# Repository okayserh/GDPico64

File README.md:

# GDPico64
Raspberry pico based graphics card to emulate an 80s EF9365 based graphics card to be used in conjunction with a modular 8 bit Z80 based computer system.

# Background
In the mid/late 80s, german public television broadcasted a series of 26 episodes of a stepwise introduction to microcomputer technology. It started with the usual stuff like binary logic, memory and the purpose of a central processing unit. Parallel to the explanations the series worked on building a modular 8 bit microcomputer, which was based on an 8 bit bus system. While the basic system used the Z80 CPU, it was possible to extend the system to an 68008 CPU board and with some tricks even to an 68020 CPU.
A full set of information and the required software is available on the following website (most of it is in german language):
www.ndr-nkc.de
In its modular setup it is conceptually very similar to the RC2014* project.

# Project
One cornerstone of the modular computer system was the graphics card named GDP64, where the 64 stands for 64kB of dedicated graphics memory, which offered 4 separate pages of 512x256 monochrome pixels (rather hi-res for that time!). The GDP64 was designed around the EF9365 graphics chip, which seems to have been one of the first graphics chips to offer a hardware implementation of graphics primitives like lines or characters. Since the chip has a MAME (www.mamedev.org) implementation, it seems to have found some use outside of this modular computer project but overall it is rather exotic. While the line drawing performance was quite impressive for its time with up to 1 Mio. Pixels/s, it lacked some features like scrolling or dedicated text modes.

This project uses the capabilities of the RP2040 to create a graphics output to support halfway modern displays (i.e. it produces an analog VGA signal where the current preferred resolution is 1920x1080@60Hz). Furthermore, the RP2040 provides a parallel interface to enable use of the GDPico64 in the same environment as the original.

As some GPIOs were free after having 8 Bit Color VGA output and the parallel bus, the board offers a PS/2 interface to connect a keyboard (this emulates the old KEY group). As an additional means of interfacing with the Z80 system, the Pico's stdio functionaliy (i.e. UART via USB) can also be used as keyboard input.

# Installation
The project assumes that the standard Pico SDK has been setup as documented in the official docs.

First the repository needs to be cloned into a separate directory:
```
git clone https://github.com/okayserh/GDPico64
```

Submodules are used to provide the FreeRTOS functions. These need to be cloned by:
```
git submodule update --init
```

For compiling the code a build directory needs to be setup with subsequent use of the CMake system
```
mkdir build
cd build
cmake ..
```

Building is than just
```
make
```

Installation on the Pico board follows the standard procedure. I.e. the .uf2 file created by the
build process is copied onto the drive presented by the Pico board.

# Usage
For the beginning, it is suggested to have a serial interface via USB. Once the initialization is completed, the monitor switches to "terminal" mode. In "terminal mode", the input received via the stdio serial interface is forwarded as key press to the Z80 system. Thus, the host keyboard can be used as input for the Z80 system. Pressing the ESC key of the host system, the software switches to "monitor mode". In monitor mode the following functions are available:

* X XModem receive
* S XModem send
* D Dump XModem buffer
* T Terminal mode
* I Dump IO buffer
* C Reset CAS bufptr
* R Reset Z80

The three functions XModem receive XModem send and Reset CAS bufptr are linked to the emulation of the original cassette interface (CAS). This interface uses a 6850 UART to convert data streams into recordable audio. The emulation uses a 4k buffer in RAM as a substitute for the cassette. The buffer can be filled from the host computer or the Z80. When the buffer has been filled via XModem, the pointer can be reset (via C) and the Z80 can read the data via the emulated 6850 interface. This allows the transmission of programs into the Z80 environment via XModem. For the opposite direction, the pointer into the buffer should be reset and the transmission from the Z80 be started. When the buffer has been filled, the XModem buffer can be send to the host computer via XModem.

With the "Dump XModel buffer" function, the current content of the cassette buffer can be displayed through the serial interface via USB.

As a debugging function, "Dump IO buffer" outputs all 256 IO registers that are used internally to emulate the different IO devices.

Finally, the "Reset Z80" function sends a reset signal via the Z80 bus and reinitializes the PIO handling the parallel bus.

# Remarks and TODOs
* As this is a weekend project, the code is not yet very nice from a software engineering or code quality perspective. Time allowing, the code quality will be improved and maybe also new features will be added.
* For many of the functions that are implemented in the code, I've been looking for sources to get some inspiration (DMA based LUT mapping, parallel port implementation). While there are some codes, I still think that the code may provide some insights into how those tasks could be done if these things should become part of another project.
* FreeRTOS was added in a later stage of the project as multiple things need to be monitored simultaneously and the initial simple scheduler became overly complex. Usage of FreeRTOS may not always be as it should be. But for the time being the code seems to work.
* The monitor is rather simple and only accessible from the USB serial interface. A possible extension would be to use the graphics output to provide a stand-alone monitor program that can be used to confgure the system
* Another extension would be to use the 8 bit color output to provide a color capable graphics interface. A simple concept would use the 4 pages as 4 bits encoding the color through the lookup table.
* Generally it is also conceivable to complete change the graphics interface into something more like an 80s homecomputer graphics.
* Addition of the floppy controller to enable the use of CP/M.

# Trademarks
    "RC2014" is a registered trademark of RFC2795 Ltd.
    Other names and brands may be claimed as the property of others.

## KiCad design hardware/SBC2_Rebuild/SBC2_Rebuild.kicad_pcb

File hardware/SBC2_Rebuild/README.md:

# SBC2 "Rebuild"
The SBC2 was a card that included the Z80 CPU, 8k of EPROM and 4k of RAM on a single PCB. The EPROM was mapped to 0x0000-0x2000, while the RAM was located from 0x8000 to 0x9000. In order to have a complete system on the PCB, an oscillator circuit and the reset logic were also implemented on the board.

It is important to note, that this board was merely enough to use the basic program ("grundprogramm"), which could be considered a simple monitor with extensions to enter simple machine code programs and to write those programs to the cassette interface. For user interested in getting more from the modular concept, separate cards with distinct CPUs and Memories were offered. By using these cards, the system could be extended to 1MB of memory with some bank logic. In those configurations it was also possible to use the system together with CP/M.

Since my original SBC2 board was messed up with wrong solders, I decided to redraw the SBC2 with KiCad and order replacements from a PCB shop. The result can be found in this folder.

# Remarks:
The required memory types 2732 and 6116 are hard to come by today. With hindsight bias, it was not such a good idea to spend time to replicate this design. In my current working setup, the card is only populated with a single 6116, while the sockets are filled with wires to forward the address lines that are not provided to the bus in the original design. Also the reset logic is left unpopulated as the reset must be provided by the GDPico64 in order to have the parallel bus set up properly. Henc,e, in my working setup it is mostly used ad clock generator and holder for the Z80 CPU.
Another point which seems not quite up to date is the dimensioning of the pull-up resistors. Those are 1k resistors, which to me seem rather strong by current CMOS standards.
The logic for the clock generation works, but the signal is not very good. Using an off the shelve oscillator might have been a better option for the redesign.

# Licensing
The copyright of the original PCB design is by Rolf Dieter Klein, who was the mastermind behind the whole computer system
Copyright of PCB layouts seems to be a bit difficult. My understanding is that schematics cannot be copyrighted. However, individual layouts can be subject of copyright. In this work I've recreated the original layout in KiCad with some minimal modifications in routing. I don't know if this suffices to grant me the copyright on this design.
In case anyone feels that this design violates his/her copyright, please drop me a note and I'll take this part of the project offline.

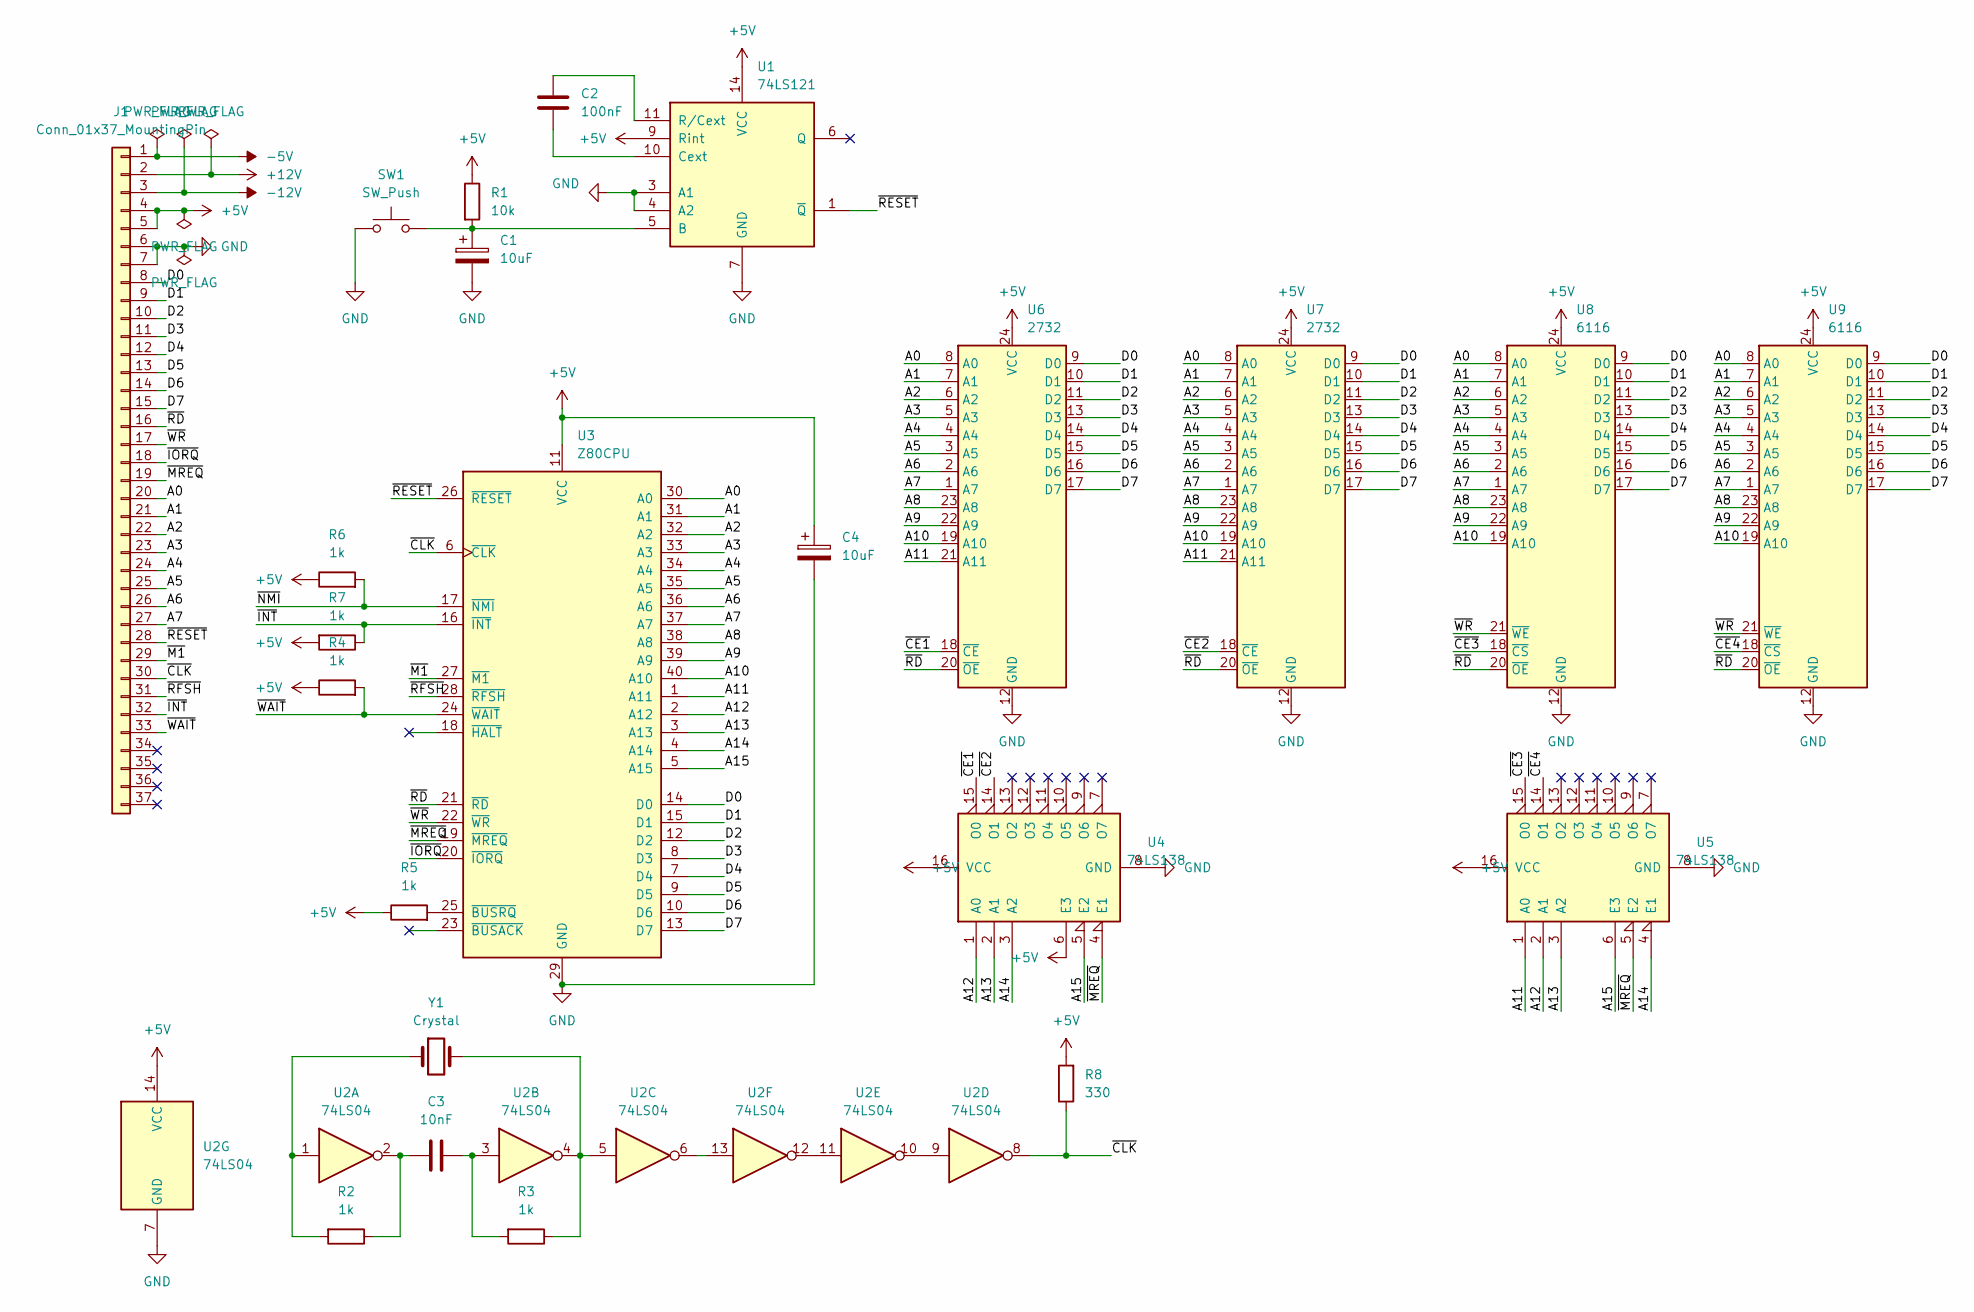
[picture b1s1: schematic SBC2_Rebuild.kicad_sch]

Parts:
C1, C4: 10uF; CP_Radial_Tantal_D4.5mm_P5.00mm
C2: 100nF; C_Disc_D5.0mm_W2.5mm_P5.00mm
C3: 10nF; C_Disc_D5.0mm_W2.5mm_P5.00mm
J1: Conn_01x37_MountingPin; PinHeader_1x37_P2.54mm_Horizontal
R1: 10k; R_Axial_DIN0207_L6.3mm_D2.5mm_P10.16mm_Horizontal
R2, R3, R4, R5, R6, R7: 1k; R_Axial_DIN0207_L6.3mm_D2.5mm_P10.16mm_Horizontal
R8: 330; R_Axial_DIN0207_L6.3mm_D2.5mm_P10.16mm_Horizontal
SW1: SW_Push; PinHeader_1x02_P2.54mm_Vertical
U1: 74LS121; DIP-14_W7.62mm_Socket
U2: 74LS04; DIP-14_W7.62mm_Socket
U3: Z80CPU; DIP-40_W15.24mm_Socket
U4, U5: 74LS138; DIP-16_W7.62mm_Socket
U6, U7: 2732; DIP-24_W15.24mm_Socket
U8, U9: 6116; DIP-24_W15.24mm_Socket
Y1: Crystal; Crystal_HC18-U_Vertical

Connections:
+5V: C4.1, J1.4, J1.5, R1.1, R4.1, R5.1, R6.1, R7.2, R8.2, U1.9 (Rint), U1.14 (VCC), U2.14 (VCC), U3.11 (VCC), U4.6 (E3), U4.16 (VCC), U5.16 (VCC), U6.24 (VCC), U7.24 (VCC), U8.24 (VCC), U9.24 (VCC)
+12V: J1.2
-5V: J1.1
-12V: J1.3
/A0: J1.20, U3.30 (A0), U6.8 (A0), U7.8 (A0), U8.8 (A0), U9.8 (A0)
/A1: J1.21, U3.31 (A1), U6.7 (A1), U7.7 (A1), U8.7 (A1), U9.7 (A1)
/A2: J1.22, U3.32 (A2), U6.6 (A2), U7.6 (A2), U8.6 (A2), U9.6 (A2)
/A3: J1.23, U3.33 (A3), U6.5 (A3), U7.5 (A3), U8.5 (A3), U9.5 (A3)
/A4: J1.24, U3.34 (A4), U6.4 (A4), U7.4 (A4), U8.4 (A4), U9.4 (A4)
/A5: J1.25, U3.35 (A5), U6.3 (A5), U7.3 (A5), U8.3 (A5), U9.3 (A5)
/A6: J1.26, U3.36 (A6), U6.2 (A6), U7.2 (A6), U8.2 (A6), U9.2 (A6)
/A7: J1.27, U3.37 (A7), U6.1 (A7), U7.1 (A7), U8.1 (A7), U9.1 (A7)
/A8: U3.38 (A8), U6.23 (A8), U7.23 (A8), U8.23 (A8), U9.23 (A8)
/A9: U3.39 (A9), U6.22 (A9), U7.22 (A9), U8.22 (A9), U9.22 (A9)
/A10: U3.40 (A10), U6.19 (A10), U7.19 (A10), U8.19 (A10), U9.19 (A10)
/A11: U3.1 (A11), U5.1 (A0), U6.21 (A11), U7.21 (A11)
/A12: U3.2 (A12), U4.1 (A0), U5.2 (A1)
/A13: U3.3 (A13), U4.2 (A1), U5.3 (A2)
/A14: U3.4 (A14), U4.3 (A2), U5.4 (E1)
/A15: U3.5 (A15), U4.5 (E2), U5.6 (E3)
/D0: J1.8, U3.14 (D0), U6.9 (D0), U7.9 (D0), U8.9 (D0), U9.9 (D0)
/D1: J1.9, U3.15 (D1), U6.10 (D1), U7.10 (D1), U8.10 (D1), U9.10 (D1)
/D2: J1.10, U3.12 (D2), U6.11 (D2), U7.11 (D2), U8.11 (D2), U9.11 (D2)
/D3: J1.11, U3.8 (D3), U6.13 (D3), U7.13 (D3), U8.13 (D3), U9.13 (D3)
/D4: J1.12, U3.7 (D4), U6.14 (D4), U7.14 (D4), U8.14 (D4), U9.14 (D4)
/D5: J1.13, U3.9 (D5), U6.15 (D5), U7.15 (D5), U8.15 (D5), U9.15 (D5)
/D6: J1.14, U3.10 (D6), U6.16 (D6), U7.16 (D6), U8.16 (D6), U9.16 (D6)
/D7: J1.15, U3.13 (D7), U6.17 (D7), U7.17 (D7), U8.17 (D7), U9.17 (D7)
/~CE1: U4.15 (O0), U6.18 (~CE)
/~CE2: U4.14 (O1), U7.18 (~CE)
/~CE3: U5.15 (O0), U8.18 (~CS)
/~CE4: U5.14 (O1), U9.18 (~CS)
/~CLK: J1.30, R8.1, U2.8, U3.6 (~CLK)
/~INT: J1.32, R7.1, U3.16 (~INT)
/~IORQ: J1.18, U3.20 (~IORQ)
/~M1: J1.29, U3.27 (~M1)
/~MREQ: J1.19, U3.19 (~MREQ), U4.4 (E1), U5.5 (E2)
/~NMI: R6.2, U3.17 (~NMI)
/~RD: J1.16, U3.21 (~RD), U6.20 (~OE), U7.20 (~OE), U8.20 (~OE), U9.20 (~OE)
/~RESET: J1.28, U1.1 (~Q), U3.26 (~RESET)
/~RFSH: J1.31, U3.28 (~RFSH)
/~WAIT: J1.33, R4.2, U3.24 (~WAIT)
/~WR: J1.17, U3.22 (~WR), U8.21 (~WE), U9.21 (~WE)
GND: C1.2, C4.2, J1.6, J1.7, SW1.1, U1.3 (A1), U1.4 (A2), U1.7 (GND), U2.7 (GND), U3.29 (GND), U4.8 (GND), U5.8 (GND), U6.12 (GND), U7.12 (GND), U8.12 (GND), U9.12 (GND)
unnamed: C1.1, R1.2, SW1.2, U1.5 (B)
unnamed: C2.1, U1.11 (R/Cext)
unnamed: C2.2, U1.10 (Cext)
unnamed: C3.1, R3.2, U2.3
unnamed: C3.2, R2.1, U2.2
unnamed: R2.2, U2.1, Y1.1
unnamed: R3.1, U2.4, U2.5, Y1.2
unnamed: R5.2, U3.25 (~BUSRQ)
unnamed: U2.9, U2.10
unnamed: U2.11, U2.12
unnamed: U2.6, U2.13

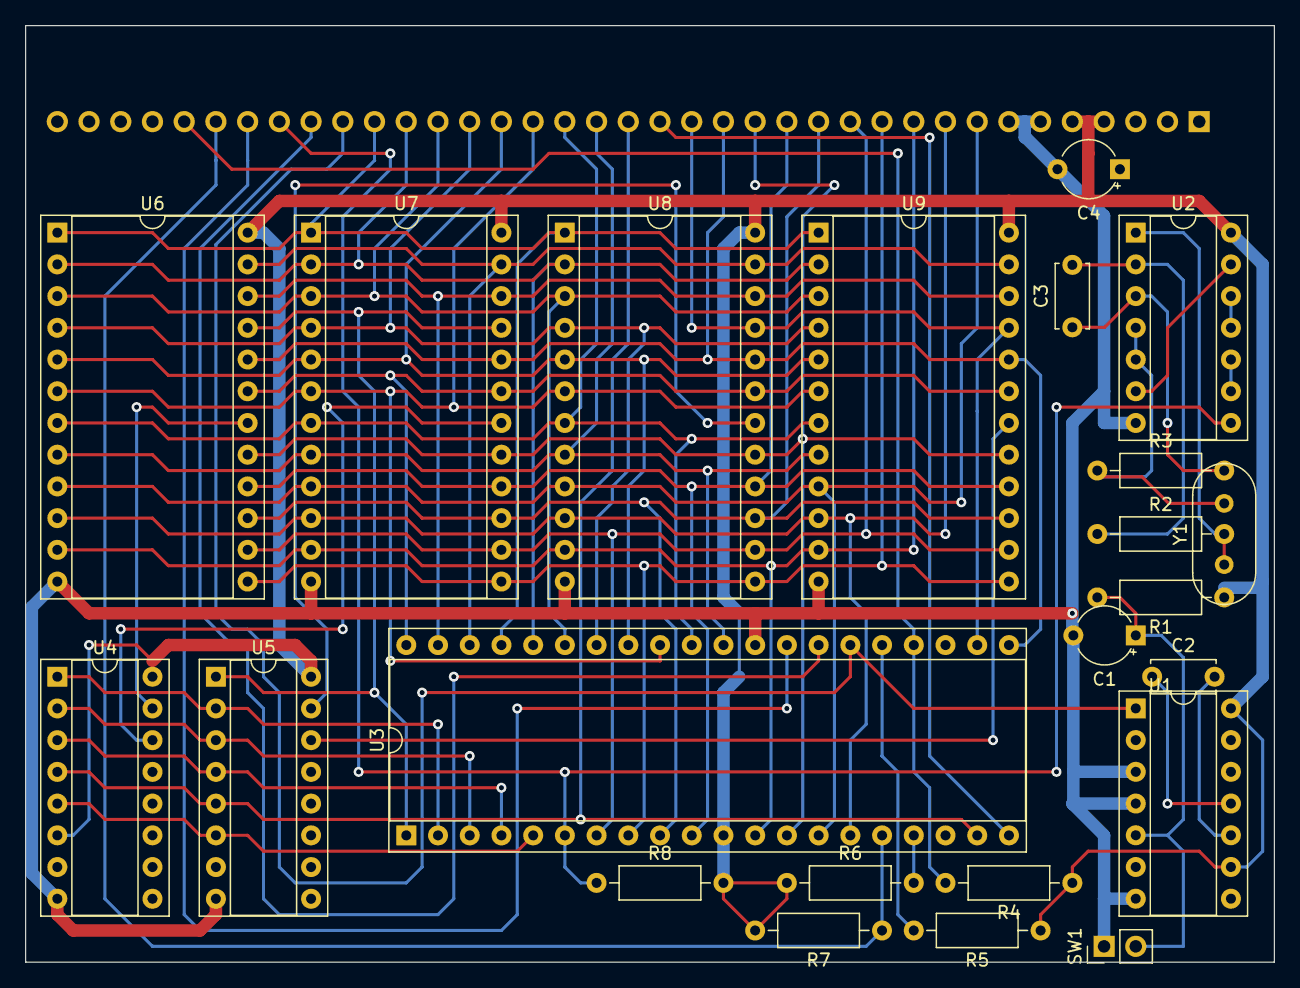
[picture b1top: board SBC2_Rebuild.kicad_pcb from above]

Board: 2 copper layers, 100.0 x 75.0 mm, 24 parts (1 on the bottom side), 52 nets.

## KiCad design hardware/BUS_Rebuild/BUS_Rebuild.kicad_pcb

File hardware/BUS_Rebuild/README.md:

# BUS "Rebuild"
The BUS group was at the heart of the modular computer system. It provided a bus for 6 PCBs that usually included the CPU, some memory cards and some IO respectively Graphics cards.

Since the original PCBs are "unobtainium", I've spend an evening redesigning the original BUS backplane. I've made a few minor modifications to the original layout.

# Licensing

The hardware design itself, including schematic and PCB layout design files are licensed under the strongly-reciprocal variant of [CERN Open Hardware Licence version 2](license-cern_ohl_s_v2.txt).

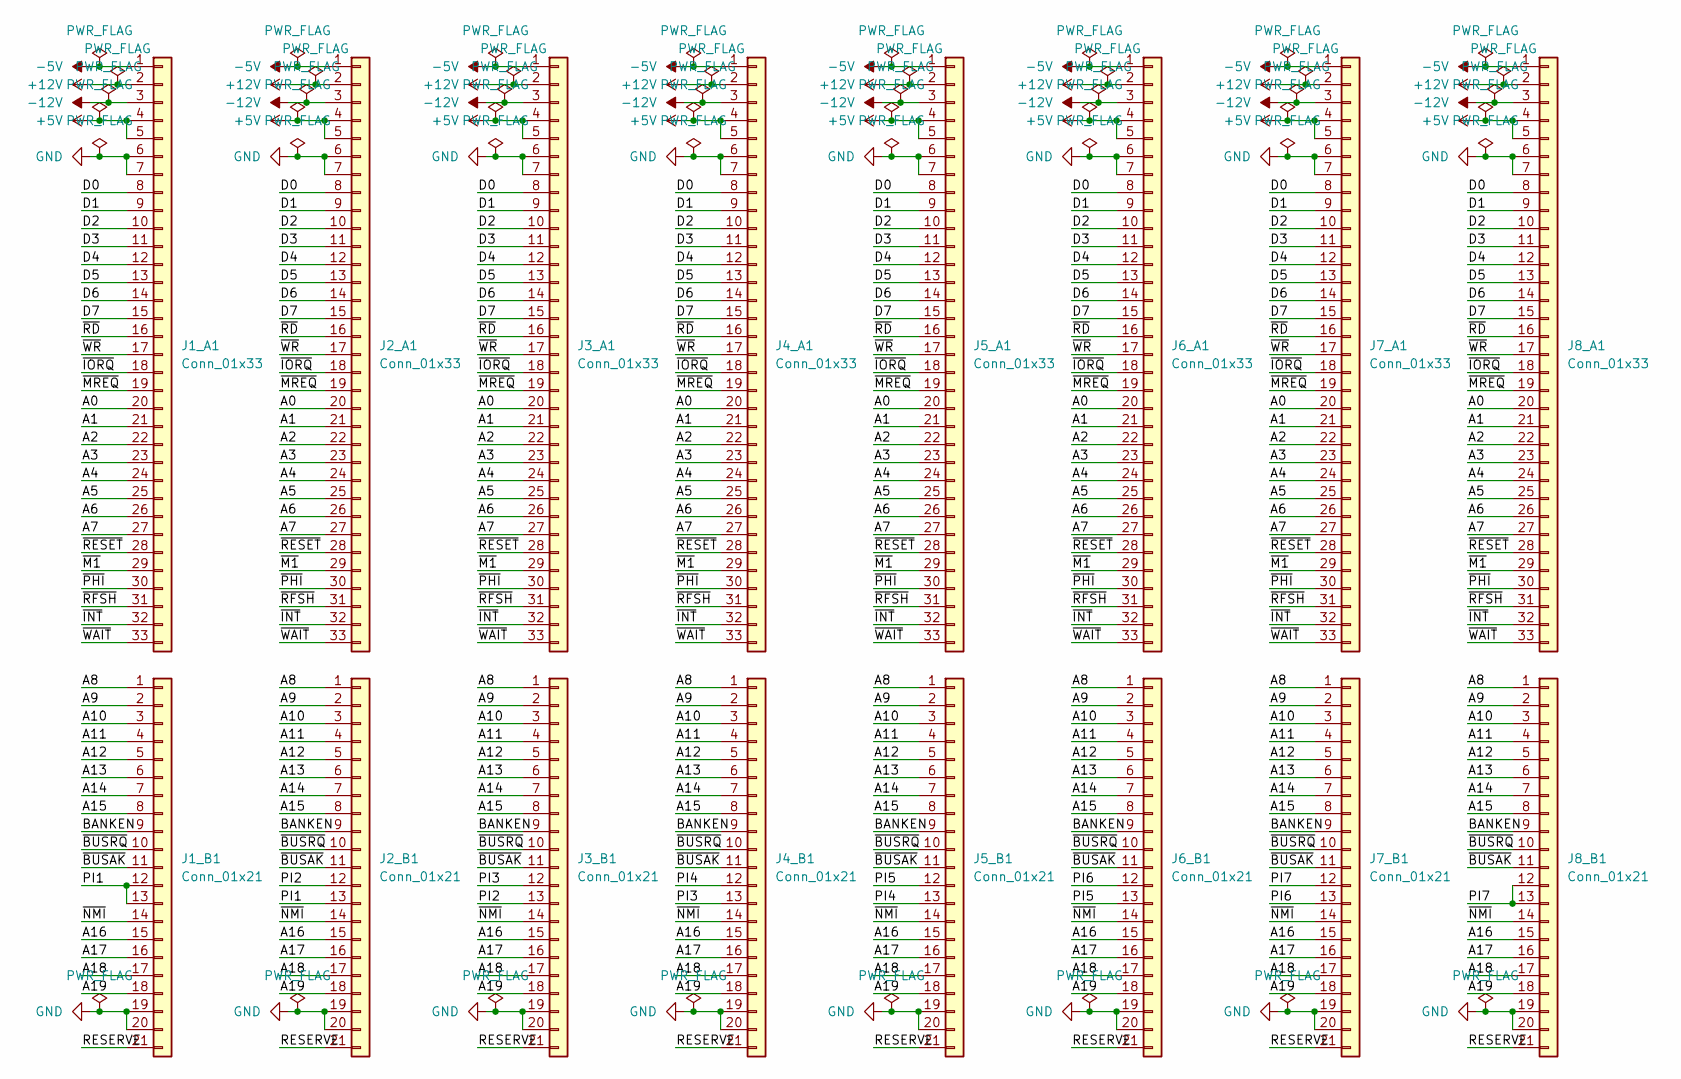
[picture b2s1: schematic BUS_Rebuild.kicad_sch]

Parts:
J1_A1, J2_A1, J3_A1, J4_A1, J5_A1, J6_A1, J7_A1, J8_A1: Conn_01x33; PinSocket_1x33_P2.54mm_Vertical
J1_B1, J2_B1, J3_B1, J4_B1, J5_B1, J6_B1, J7_B1, J8_B1: Conn_01x21; PinSocket_1x21_P2.54mm_Vertical

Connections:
+5V: J1_A1.4, J1_A1.5, J2_A1.4, J2_A1.5, J3_A1.4, J3_A1.5, J4_A1.4, J4_A1.5, J5_A1.4, J5_A1.5, J6_A1.4, J6_A1.5, J7_A1.4, J7_A1.5, J8_A1.4, J8_A1.5
+12V: J1_A1.2, J2_A1.2, J3_A1.2, J4_A1.2, J5_A1.2, J6_A1.2, J7_A1.2, J8_A1.2
-5V: J1_A1.1, J2_A1.1, J3_A1.1, J4_A1.1, J5_A1.1, J6_A1.1, J7_A1.1, J8_A1.1
-12V: J1_A1.3, J2_A1.3, J3_A1.3, J4_A1.3, J5_A1.3, J6_A1.3, J7_A1.3, J8_A1.3
/A0: J1_A1.20, J2_A1.20, J3_A1.20, J4_A1.20, J5_A1.20, J6_A1.20, J7_A1.20, J8_A1.20
/A1: J1_A1.21, J2_A1.21, J3_A1.21, J4_A1.21, J5_A1.21, J6_A1.21, J7_A1.21, J8_A1.21
/A2: J1_A1.22, J2_A1.22, J3_A1.22, J4_A1.22, J5_A1.22, J6_A1.22, J7_A1.22, J8_A1.22
/A3: J1_A1.23, J2_A1.23, J3_A1.23, J4_A1.23, J5_A1.23, J6_A1.23, J7_A1.23, J8_A1.23
/A4: J1_A1.24, J2_A1.24, J3_A1.24, J4_A1.24, J5_A1.24, J6_A1.24, J7_A1.24, J8_A1.24
/A5: J1_A1.25, J2_A1.25, J3_A1.25, J4_A1.25, J5_A1.25, J6_A1.25, J7_A1.25, J8_A1.25
/A6: J1_A1.26, J2_A1.26, J3_A1.26, J4_A1.26, J5_A1.26, J6_A1.26, J7_A1.26, J8_A1.26
/A7: J1_A1.27, J2_A1.27, J3_A1.27, J4_A1.27, J5_A1.27, J6_A1.27, J7_A1.27, J8_A1.27
/A8: J1_B1.1, J2_B1.1, J3_B1.1, J4_B1.1, J5_B1.1, J6_B1.1, J7_B1.1, J8_B1.1
/A9: J1_B1.2, J2_B1.2, J3_B1.2, J4_B1.2, J5_B1.2, J6_B1.2, J7_B1.2, J8_B1.2
/A10: J1_B1.3, J2_B1.3, J3_B1.3, J4_B1.3, J5_B1.3, J6_B1.3, J7_B1.3, J8_B1.3
/A11: J1_B1.4, J2_B1.4, J3_B1.4, J4_B1.4, J5_B1.4, J6_B1.4, J7_B1.4, J8_B1.4
/A12: J1_B1.5, J2_B1.5, J3_B1.5, J4_B1.5, J5_B1.5, J6_B1.5, J7_B1.5, J8_B1.5
/A13: J1_B1.6, J2_B1.6, J3_B1.6, J4_B1.6, J5_B1.6, J6_B1.6, J7_B1.6, J8_B1.6
/A14: J1_B1.7, J2_B1.7, J3_B1.7, J4_B1.7, J5_B1.7, J6_B1.7, J7_B1.7, J8_B1.7
/A15: J1_B1.8, J2_B1.8, J3_B1.8, J4_B1.8, J5_B1.8, J6_B1.8, J7_B1.8, J8_B1.8
/A16: J1_B1.15, J2_B1.15, J3_B1.15, J4_B1.15, J5_B1.15, J6_B1.15, J7_B1.15, J8_B1.15
/A17: J1_B1.16, J2_B1.16, J3_B1.16, J4_B1.16, J5_B1.16, J6_B1.16, J7_B1.16, J8_B1.16
/A18: J1_B1.17, J2_B1.17, J3_B1.17, J4_B1.17, J5_B1.17, J6_B1.17, J7_B1.17, J8_B1.17
/A19: J1_B1.18, J2_B1.18, J3_B1.18, J4_B1.18, J5_B1.18, J6_B1.18, J7_B1.18, J8_B1.18
/BANKEN: J1_B1.9, J2_B1.9, J3_B1.9, J4_B1.9, J5_B1.9, J6_B1.9, J7_B1.9, J8_B1.9
/D0: J1_A1.8, J2_A1.8, J3_A1.8, J4_A1.8, J5_A1.8, J6_A1.8, J7_A1.8, J8_A1.8
/D1: J1_A1.9, J2_A1.9, J3_A1.9, J4_A1.9, J5_A1.9, J6_A1.9, J7_A1.9, J8_A1.9
/D2: J1_A1.10, J2_A1.10, J3_A1.10, J4_A1.10, J5_A1.10, J6_A1.10, J7_A1.10, J8_A1.10
/D3: J1_A1.11, J2_A1.11, J3_A1.11, J4_A1.11, J5_A1.11, J6_A1.11, J7_A1.11, J8_A1.11
/D4: J1_A1.12, J2_A1.12, J3_A1.12, J4_A1.12, J5_A1.12, J6_A1.12, J7_A1.12, J8_A1.12
/D5: J1_A1.13, J2_A1.13, J3_A1.13, J4_A1.13, J5_A1.13, J6_A1.13, J7_A1.13, J8_A1.13
/D6: J1_A1.14, J2_A1.14, J3_A1.14, J4_A1.14, J5_A1.14, J6_A1.14, J7_A1.14, J8_A1.14
/D7: J1_A1.15, J2_A1.15, J3_A1.15, J4_A1.15, J5_A1.15, J6_A1.15, J7_A1.15, J8_A1.15
/PI1: J1_B1.12, J1_B1.13, J2_B1.13
/PI2: J2_B1.12, J3_B1.13
/PI3: J3_B1.12, J4_B1.13
/PI4: J4_B1.12, J5_B1.13
/PI5: J5_B1.12, J6_B1.13
/PI6: J6_B1.12, J7_B1.13
/PI7: J7_B1.12, J8_B1.12, J8_B1.13
/RESERVE: J1_B1.21, J2_B1.21, J3_B1.21, J4_B1.21, J5_B1.21, J6_B1.21, J7_B1.21, J8_B1.21
/~BUSAK: J1_B1.11, J2_B1.11, J3_B1.11, J4_B1.11, J5_B1.11, J6_B1.11, J7_B1.11, J8_B1.11
/~BUSRQ: J1_B1.10, J2_B1.10, J3_B1.10, J4_B1.10, J5_B1.10, J6_B1.10, J7_B1.10, J8_B1.10
/~INT: J1_A1.32, J2_A1.32, J3_A1.32, J4_A1.32, J5_A1.32, J6_A1.32, J7_A1.32, J8_A1.32
/~IORQ: J1_A1.18, J2_A1.18, J3_A1.18, J4_A1.18, J5_A1.18, J6_A1.18, J7_A1.18, J8_A1.18
/~M1: J1_A1.29, J2_A1.29, J3_A1.29, J4_A1.29, J5_A1.29, J6_A1.29, J7_A1.29, J8_A1.29
/~MREQ: J1_A1.19, J2_A1.19, J3_A1.19, J4_A1.19, J5_A1.19, J6_A1.19, J7_A1.19, J8_A1.19
/~NMI: J1_B1.14, J2_B1.14, J3_B1.14, J4_B1.14, J5_B1.14, J6_B1.14, J7_B1.14, J8_B1.14
/~PHI: J1_A1.30, J2_A1.30, J3_A1.30, J4_A1.30, J5_A1.30, J6_A1.30, J7_A1.30, J8_A1.30
/~RD: J1_A1.16, J2_A1.16, J3_A1.16, J4_A1.16, J5_A1.16, J6_A1.16, J7_A1.16, J8_A1.16
/~RESET: J1_A1.28, J2_A1.28, J3_A1.28, J4_A1.28, J5_A1.28, J6_A1.28, J7_A1.28, J8_A1.28
/~RFSH: J1_A1.31, J2_A1.31, J3_A1.31, J4_A1.31, J5_A1.31, J6_A1.31, J7_A1.31, J8_A1.31
/~WAIT: J1_A1.33, J2_A1.33, J3_A1.33, J4_A1.33, J5_A1.33, J6_A1.33, J7_A1.33, J8_A1.33
/~WR: J1_A1.17, J2_A1.17, J3_A1.17, J4_A1.17, J5_A1.17, J6_A1.17, J7_A1.17, J8_A1.17
GND: J1_A1.6, J1_A1.7, J1_B1.19, J1_B1.20, J2_A1.6, J2_A1.7, J2_B1.19, J2_B1.20, J3_A1.6, J3_A1.7, J3_B1.19, J3_B1.20, J4_A1.6, J4_A1.7, J4_B1.19, J4_B1.20, J5_A1.6, J5_A1.7, J5_B1.19, J5_B1.20, J6_A1.6, J6_A1.7, J6_B1.19, J6_B1.20, J7_A1.6, J7_A1.7, J7_B1.19, J7_B1.20, J8_A1.6, J8_A1.7, J8_B1.19, J8_B1.20

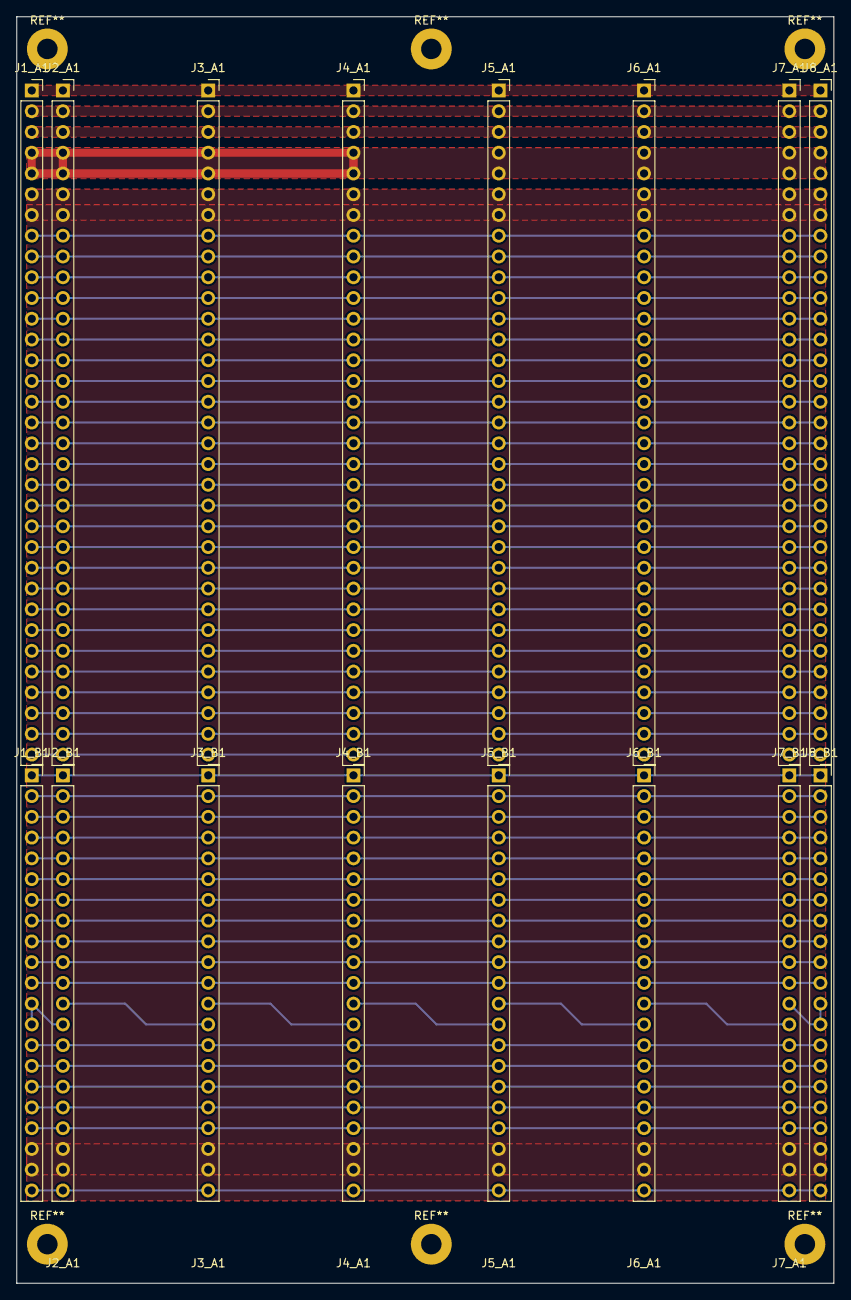
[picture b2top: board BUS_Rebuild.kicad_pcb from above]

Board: 2 copper layers, 100.0 x 155.0 mm, 16 parts (0 on the bottom side), 55 nets.

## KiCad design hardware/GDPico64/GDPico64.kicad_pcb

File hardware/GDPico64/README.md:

# GDPico64, Hardware
Raspberry pico based graphics card to emulate an 80s EF9365 based graphics card to be used in conjunction with a modular 8 bit Z80 based computer system.

# Layout and functions
Since my background is more on the software side, this is the first PCB I've developed. While it works in my setup, it may lack some features professional PCB designers or electrical engineers would add.

It uses 74245 chips to translate the Z80 bus signals into 3.3v signals that are compatible to the Pico GPIO pins. In order to save GPIOs on the Pico, the address and data part of the bus is multiplixed by using two 74245 chips. For outputting data signals to the Z80 bus, the 74245 chips are used as well. However, for the controlling the RESET and the WAIT signal an 5V inverter is used. While the 74245 worked for those signals as well in my breadboard development setup, there seems to be a risk that the 74245 is used out of spec in this setup when pull-up resitors drive the signals to 5V.

The VGA output is a simple resistor network inspired by the PICO VGA library.

Known shortcomings:
* No guarantee to do anything useful and leave other components to be used in conjuntion with this PCB undamaged! Use at your own risk!
* No protection against powering the Pico via the parallel bus and the USB port.
* As of now, only tested in a configuration where the whole system is powered through the USB port of the Pico.

# Release Notes
* Version 0.1:
  * Initial version

# Licensing

The hardware design itself, including schematic and PCB layout design files are licensed under the strongly-reciprocal variant of [CERN Open Hardware Licence version 2](license-cern_ohl_s_v2.txt).

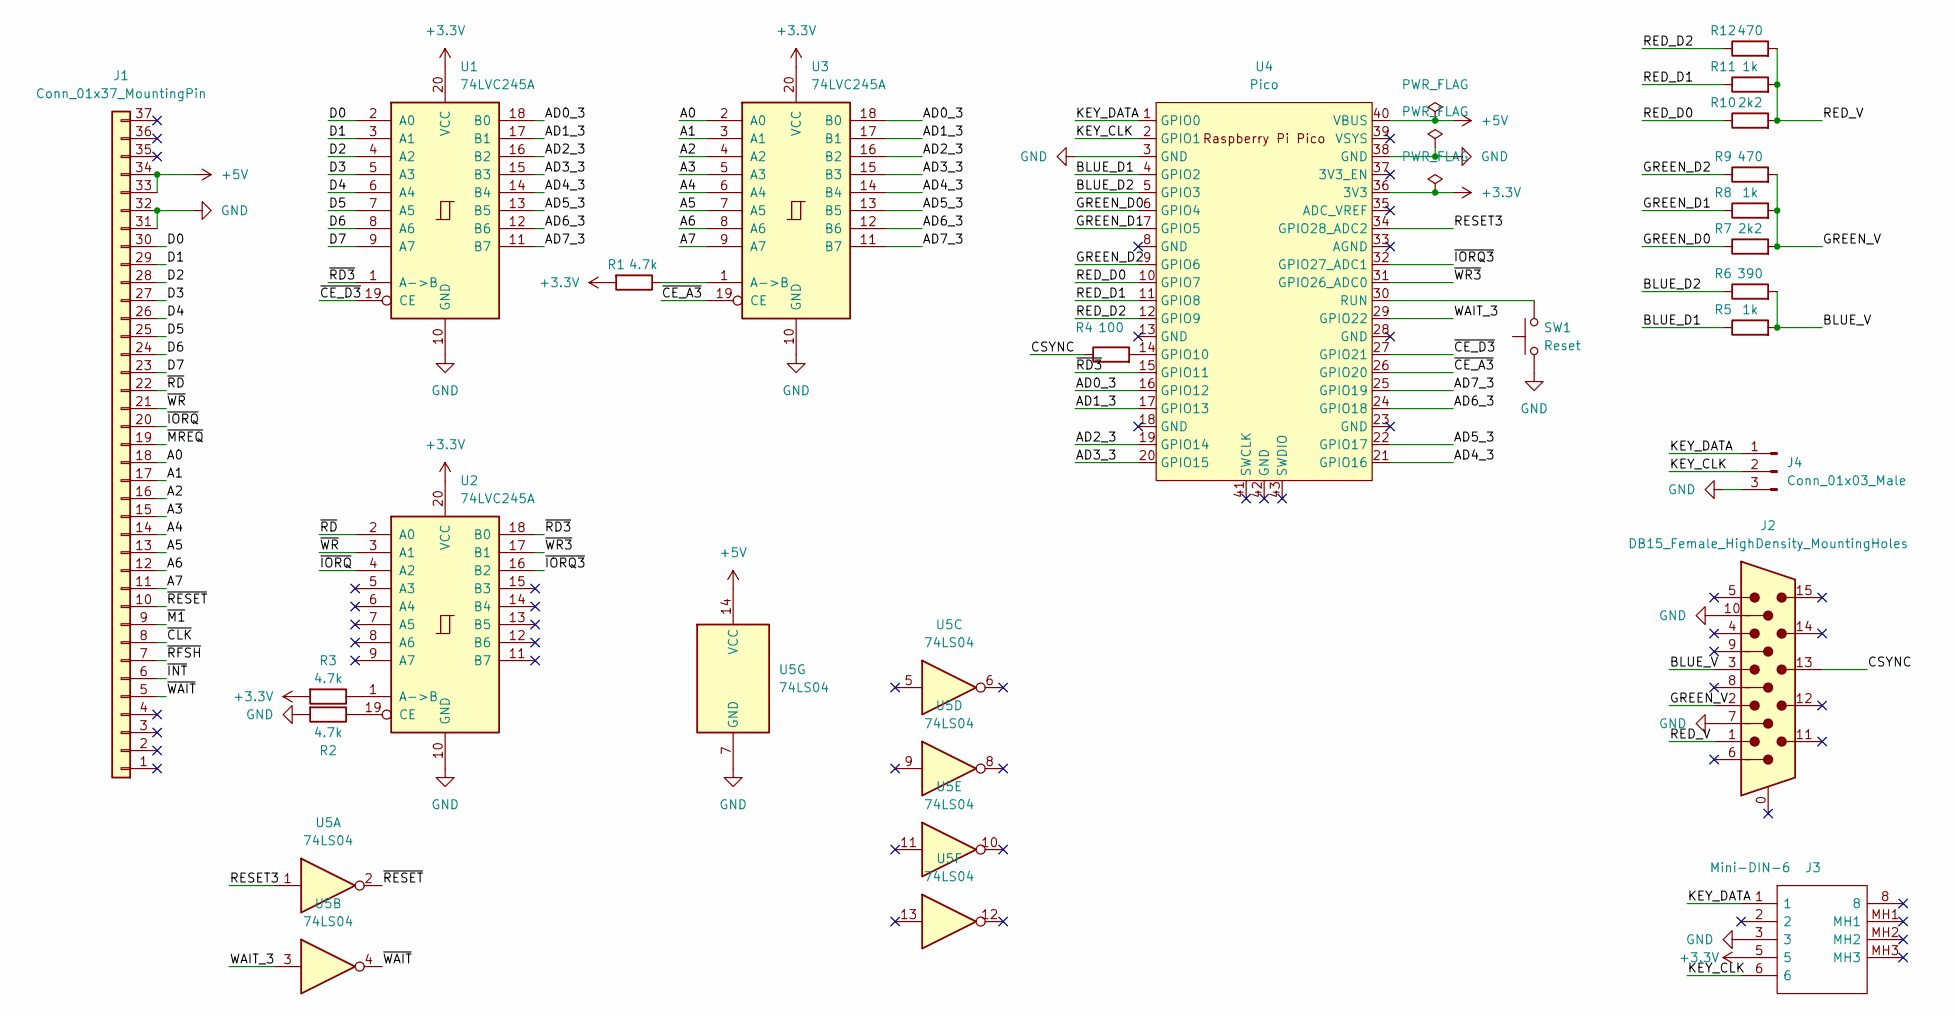
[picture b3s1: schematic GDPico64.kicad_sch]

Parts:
J1: Conn_01x37_MountingPin; PinHeader_1x37_P2.54mm_Horizontal
J2: DB15_Female_HighDensity_MountingHoles; DSUB-15-HD_Female_Horizontal_P2.29x1.98mm_EdgePinOffset8.35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
J3: Mini-DIN-6; KMDGX6SBS; Manufacturer_Part_Number KMDGX-6S-BS; Mouser Part Number 806-KMDGX-6S-BS
J4: Conn_01x03_Male; PinHeader_1x03_P2.54mm_Horizontal
R1, R2, R3: 4.7k; R_Axial_DIN0207_L6.3mm_D2.5mm_P10.16mm_Horizontal
R4: 100; R_Axial_DIN0207_L6.3mm_D2.5mm_P10.16mm_Horizontal
R5, R8, R11: 1k; R_Axial_DIN0207_L6.3mm_D2.5mm_P10.16mm_Horizontal
R6: 390; R_Axial_DIN0207_L6.3mm_D2.5mm_P10.16mm_Horizontal
R7, R10: 2k2; R_Axial_DIN0207_L6.3mm_D2.5mm_P10.16mm_Horizontal
R9, R12: 470; R_Axial_DIN0207_L6.3mm_D2.5mm_P10.16mm_Horizontal
SW1: Reset; SW_Tactile_SPST_Angled_PTS645Vx58-2LFS
U1, U2, U3: 74LVC245A; DIP-20_W7.62mm
U4: Pico; RPi_Pico_SMD_TH
U5: 74LS04; DIP-14_W7.62mm

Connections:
+3V3: J3.5, R1.2, R3.2, U1.20 (VCC), U2.20 (VCC), U3.20 (VCC), U4.36 (3V3)
+5V: J1.33, J1.34, U4.40 (VBUS), U5.14 (VCC)
/A0: J1.18, U3.2 (A0)
/A1: J1.17, U3.3 (A1)
/A2: J1.16, U3.4 (A2)
/A3: J1.15, U3.5 (A3)
/A4: J1.14, U3.6 (A4)
/A5: J1.13, U3.7 (A5)
/A6: J1.12, U3.8 (A6)
/A7: J1.11, U3.9 (A7)
/AD0_3: U1.18 (B0), U3.18 (B0), U4.16 (GPIO12)
/AD1_3: U1.17 (B1), U3.17 (B1), U4.17 (GPIO13)
/AD2_3: U1.16 (B2), U3.16 (B2), U4.19 (GPIO14)
/AD3_3: U1.15 (B3), U3.15 (B3), U4.20 (GPIO15)
/AD4_3: U1.14 (B4), U3.14 (B4), U4.21 (GPIO16)
/AD5_3: U1.13 (B5), U3.13 (B5), U4.22 (GPIO17)
/AD6_3: U1.12 (B6), U3.12 (B6), U4.24 (GPIO18)
/AD7_3: U1.11 (B7), U3.11 (B7), U4.25 (GPIO19)
/BLUE_D1: R5.1, U4.4 (GPIO2)
/BLUE_D2: R6.1, U4.5 (GPIO3)
/BLUE_V: J2.3, R5.2, R6.2
/CSYNC: J2.13, R4.1
/D0: J1.30, U1.2 (A0)
/D1: J1.29, U1.3 (A1)
/D2: J1.28, U1.4 (A2)
/D3: J1.27, U1.5 (A3)
/D4: J1.26, U1.6 (A4)
/D5: J1.25, U1.7 (A5)
/D6: J1.24, U1.8 (A6)
/D7: J1.23, U1.9 (A7)
/GREEN_D0: R7.1, U4.6 (GPIO4)
/GREEN_D1: R8.1, U4.7 (GPIO5)
/GREEN_D2: R9.1, U4.9 (GPIO6)
/GREEN_V: J2.2, R7.2, R8.2, R9.2
/KEY_CLK: J3.6, J4.2, U4.2 (GPIO1)
/KEY_DATA: J3.1, J4.1, U4.1 (GPIO0)
/RED_D0: R10.1, U4.10 (GPIO7)
/RED_D1: R11.1, U4.11 (GPIO8)
/RED_D2: R12.1, U4.12 (GPIO9)
/RED_V: J2.1, R10.2, R11.2, R12.2
/RESET3: U4.34 (GPIO28_ADC2), U5.1
/WAIT_3: U4.29 (GPIO22), U5.3
/~CE_A3: U3.19 (CE), U4.26 (GPIO20)
/~CE_D3: U1.19 (CE), U4.27 (GPIO21)
/~CLK: J1.8
/~INT: J1.6
/~IORQ3: U2.16 (B2), U4.32 (GPIO27_ADC1)
/~IORQ: J1.20, U2.4 (A2)
/~M1: J1.9
/~MREQ: J1.19
/~RD3: U1.1 (A->B), U2.18 (B0), U4.15 (GPIO11)
/~RD: J1.22, U2.2 (A0)
/~RESET: J1.10, U5.2
/~RFSH: J1.7
/~WAIT: J1.5, U5.4
/~WR3: U2.17 (B1), U4.31 (GPIO26_ADC0)
/~WR: J1.21, U2.3 (A1)
GND: J1.31, J1.32, J2.7, J2.10, J3.3, J4.3, R2.2, SW1.1, U1.10 (GND), U2.10 (GND), U3.10 (GND), U4.3 (GND), U4.38 (GND), U5.7 (GND)
unnamed: R1.1, U3.1 (A->B)
unnamed: R2.1, U2.19 (CE)
unnamed: R3.1, U2.1 (A->B)
unnamed: SW1.2, U4.30 (RUN)
unnamed: R4.2, U4.14 (GPIO10)

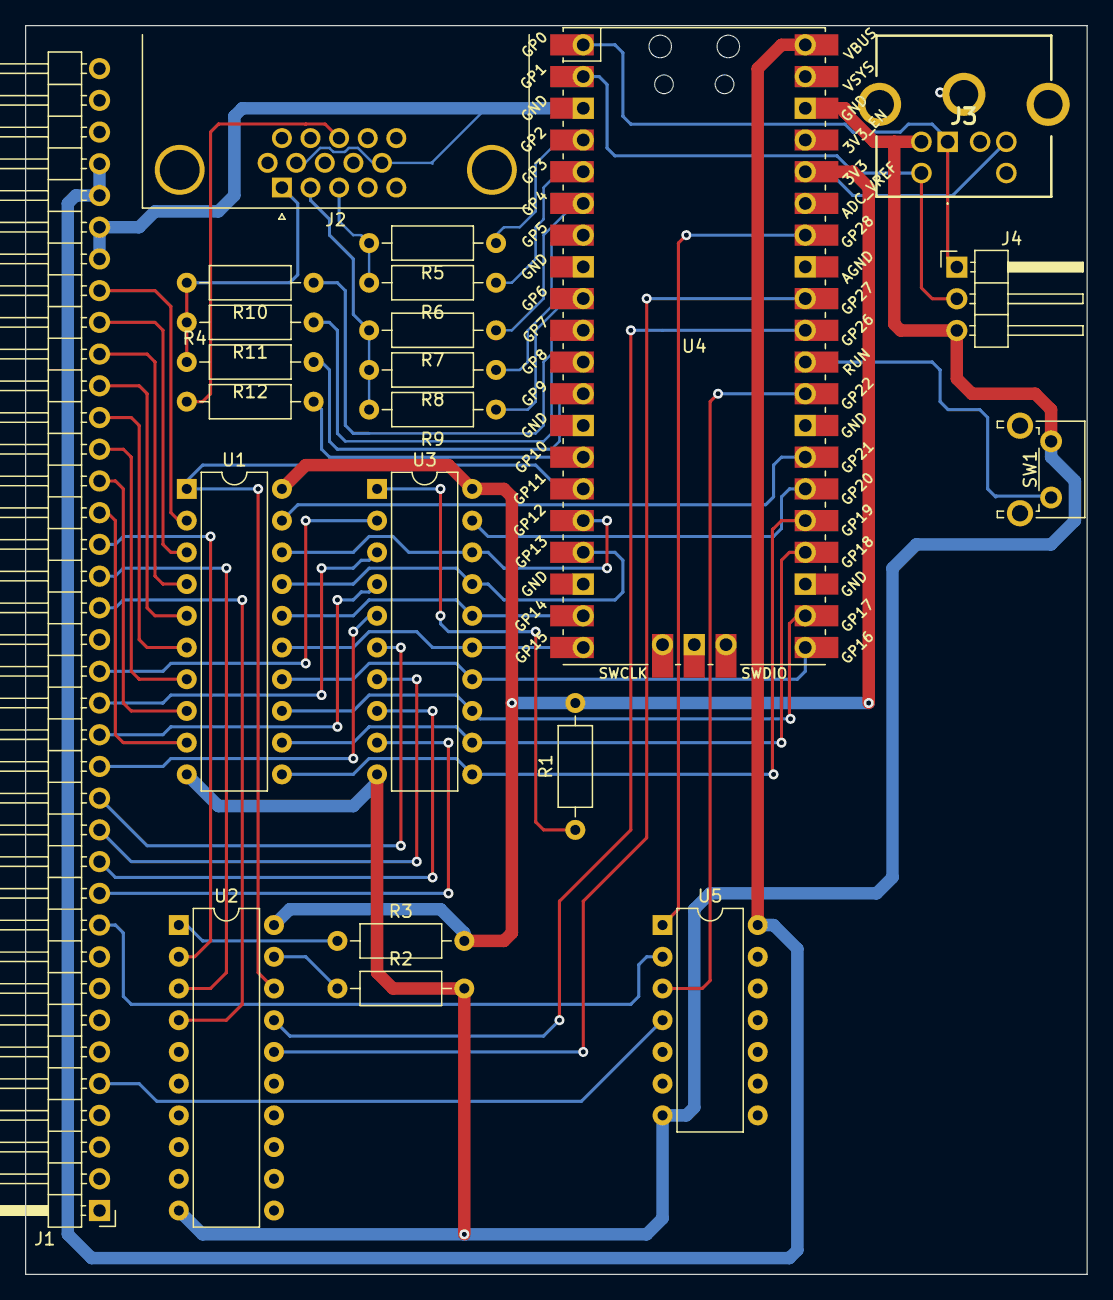
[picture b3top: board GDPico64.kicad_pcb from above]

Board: 2 copper layers, 85.0 x 100.0 mm, 22 parts (0 on the bottom side), 58 nets.

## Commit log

2024-10-05 Initial commit.
2024-10-05 Added some missing files from original development folder. Some adaptations to accomodate the most recent version of FreeRTOS.
2024-10-05 Added hardware files for BUS backplane, a rebuild of the SBC2 single board computer and the essence of this project the GDPico64 card. Added a few changes in the software.
2024-10-05 Initial readme for GDPico64 hardware.
2024-10-07 Added licenses for hardware and extended README files.
2024-10-07 Format README
2024-10-07 Formatting.
2024-10-07 Update of README
2024-10-09 Moved FreeRTOS back to V10.5.1
2024-10-09 Changed to FreeRTOS V10.5.1.
2024-10-25 Changed code to only selectively put data on the bus when an emulated device is addressed in the IO space.
